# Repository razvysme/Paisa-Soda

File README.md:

# Paisa-Soda
A triple trigger delay for Eurorack systems. - WIP

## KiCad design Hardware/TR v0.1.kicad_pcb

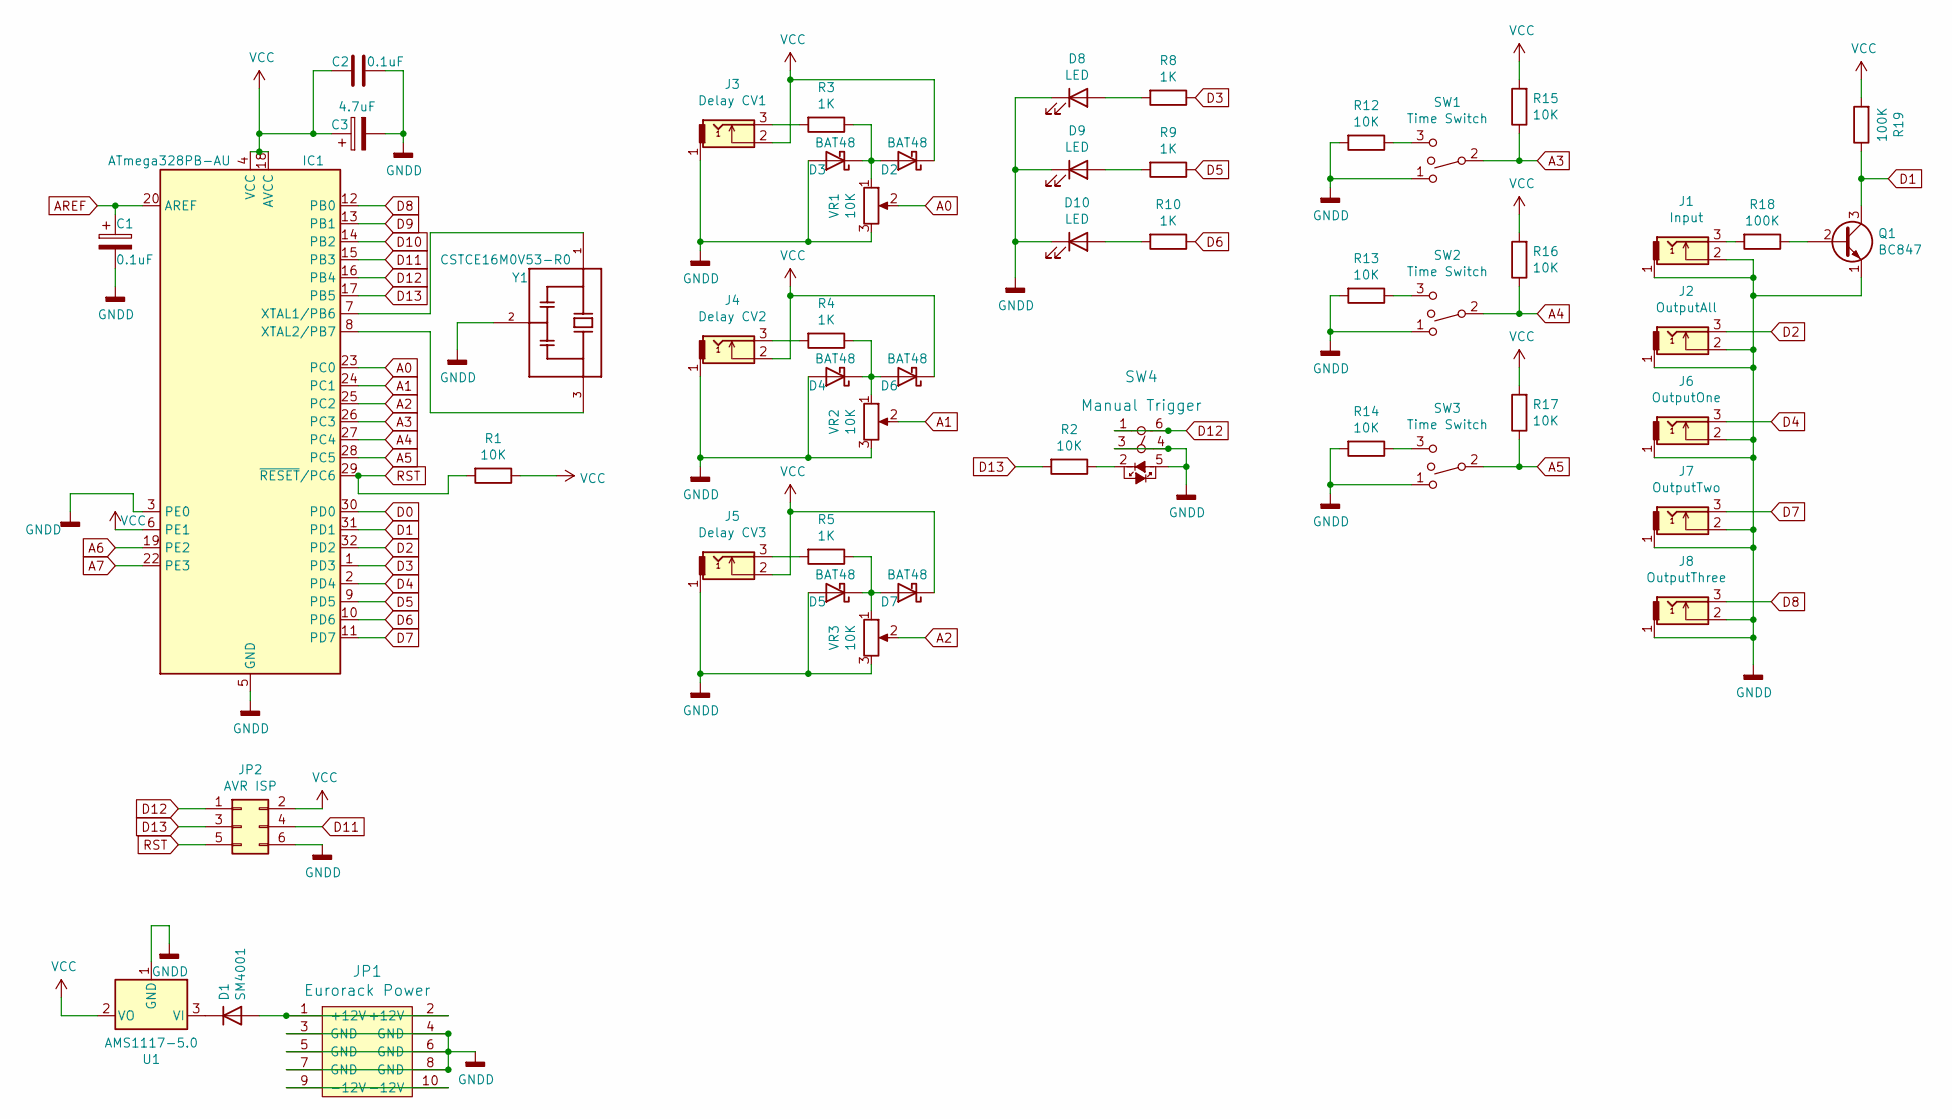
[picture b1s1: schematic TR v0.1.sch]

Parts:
C1: 0.1uF; CP_Elec_3x5.3
C2: 0.1uF; C_0805_2012Metric_Pad1.18x1.45mm_HandSolder
C3: 4.7uF; CP_Elec_3x5.3
D1: SM4001; D_SOD-323_HandSoldering
D2, D3, D4, D5, D6, D7: BAT48; D_SOD-323_HandSoldering
D8, D9, D10: LED; LED_D3.0mm_FlatTop
IC1: ATmega328PB-AU; TQFP-32_7x7mm_P0.8mm
J1: Input; thonkiconn_fuzzySi
J2: OutputAll; thonkiconn_fuzzySi
J3: Delay CV1; thonkiconn_fuzzySi
J4: Delay CV2; thonkiconn_fuzzySi
J5: Delay CV3; thonkiconn_fuzzySi
J6: OutputOne; thonkiconn_fuzzySi
J7: OutputTwo; thonkiconn_fuzzySi
J8: OutputThree; thonkiconn_fuzzySi
JP1: Eurorack Power; PinSocket_2x05_P2.54mm_Vertical
JP2: AVR ISP; PinHeader_2x03_P2.54mm_Vertical_SMD
Q1: BC847; SOT-23
R1, R2, R12, R13, R14, R15, R16, R17: 10K; R_0603_1608Metric
R3, R4, R5, R8, R9, R10: 1K; R_0603_1608Metric
R18, R19: 100K; R_0603_1608Metric
SW1, SW2, SW3: Time Switch; PinSocket_1x03_P2.54mm_Vertical
SW4: Manual Trigger; PB614_LED_SW_6pin
U1: AMS1117-5.0; SOT-223-3_TabPin2
VR1, VR2, VR3: 10K; Potentiometer_Alps_RK09L_Single_Vertical
Y1: CSTCE16M0V53-R0; OSC_CSTCE16M0V53-R0; PARTREV May 7, 2019

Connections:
A0: IC1.23 (PC0), VR1.2
A1: IC1.24 (PC1), VR2.2
A2: IC1.25 (PC2), VR3.2
A3: IC1.26 (PC3), R15.1, SW1.2
A4: IC1.27 (PC4), R16.1, SW2.2
A5: IC1.28 (PC5), R17.1, SW3.2
A6: IC1.19 (PE2)
A7: IC1.22 (PE3)
AREF: C1.1, IC1.20 (AREF)
D0: IC1.30 (PD0)
D1: IC1.31 (PD1), Q1.3 (C), R19.1
D2: IC1.32 (PD2), J2.3
D3: IC1.1 (PD3), R8.1
D4: IC1.2 (PD4), J6.3
D5: IC1.9 (PD5), R9.1
D6: IC1.10 (PD6), R10.1
D7: IC1.11 (PD7), J7.3
D8: IC1.12 (PB0), J8.3
D9: IC1.13 (PB1)
D10: IC1.14 (PB2)
D11: IC1.15 (PB3), JP2.4
D12: IC1.16 (PB4), JP2.1, SW4.1, SW4.6
D13: IC1.17 (PB5), JP2.3, R2.2
GNDD: C1.2, C2.1, C3.2, D3.2 (A), D4.2 (A), D5.2 (A), D8.1 (K), D9.1 (K), D10.1 (K), IC1.3 (PE0), IC1.5 (GND), IC1.21 (GND), J1.1, J1.2, J2.1, J2.2, J3.1, J4.1, J5.1, J6.1, J6.2, J7.1, J7.2, J8.1, J8.2, JP1.3 (GND), JP1.4 (GND), JP1.5 (GND), JP1.6 (GND), JP1.7 (GND), JP1.8 (GND), JP2.6, Q1.1 (E), R12.2, R13.2, R14.2, SW1.1, SW2.1, SW3.1, SW4.3, SW4.4, SW4.5, U1.1 (GND), VR1.3, VR2.3, VR3.3, Y1.2
unnamed: D1.1 (K), U1.3 (VI)
unnamed: D1.2 (A), JP1.1 (+12V), JP1.2 (+12V)
unnamed: D2.2 (A), D3.1 (K), R3.1, VR1.1
unnamed: D4.1 (K), D6.2 (A), R4.1, VR2.1
unnamed: D5.1 (K), D7.2 (A), R5.1, VR3.1
unnamed: D8.2 (A), R8.2
unnamed: D9.2 (A), R9.2
unnamed: D10.2 (A), R10.2
unnamed: IC1.7 (XTAL1/PB6), Y1.1
unnamed: IC1.8 (XTAL2/PB7), Y1.3
unnamed: J1.3, R18.2
unnamed: J3.3, R3.2
unnamed: J4.3, R4.2
unnamed: J5.3, R5.2
unnamed: JP1.9 (-12V), JP1.10 (-12V)
unnamed: Q1.2 (B), R18.1
unnamed: R2.1, SW4.2
unnamed: R12.1, SW1.3
unnamed: R13.1, SW2.3
unnamed: R14.1, SW3.3
RST: IC1.29 (~RESET~/PC6), JP2.5, R1.2
VCC: C2.2, C3.1, D2.1 (K), D6.1 (K), D7.1 (K), IC1.4 (VCC), IC1.6 (PE1), IC1.18 (AVCC), J3.2, J4.2, J5.2, JP2.2, R1.1, R15.2, R16.2, R17.2, R19.2, U1.2 (VO)

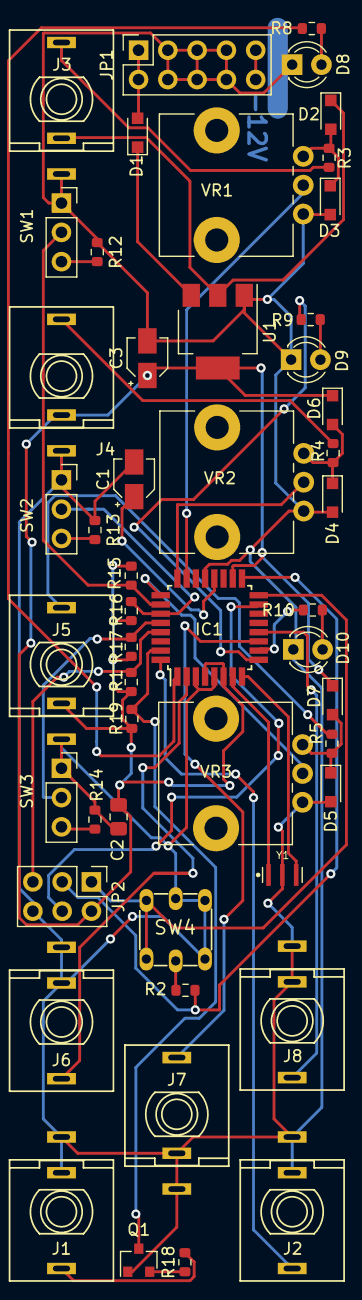
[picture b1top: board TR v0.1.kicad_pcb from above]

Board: 2 copper layers, 50 parts (0 on the bottom side), 41 nets.

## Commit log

2021-04-04 Added script
    Cascade delay works
2021-04-04 Added PCB
    Untested PCB design
2021-04-04 Changed ints to unsigned shorts; Implemented skip functionality; Next step = blinking for skipping
2021-04-04 Increased trigger Queue to 75 steps
2021-04-05 Updated Pinout and vsCode integration
2021-04-05 Added Trigger output
2021-04-05 Added Trigger Outputs
2021-04-05 Triggered not working; updated sch to match code
2021-04-06 Fixed Blinking, hold does not fully work
2021-04-06 Fixed Hold detection and mode change
2021-04-06 Updated Schematic with LED for mode
2021-04-07 Analog trigger Input working, Updt License & Sch
2021-04-10 Hold button bug, but everything else is alright.
2021-05-26 Deleted Build folder
